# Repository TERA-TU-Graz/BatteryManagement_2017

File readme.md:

# Battery Management System (BMS) with use of STM32 CubeMX

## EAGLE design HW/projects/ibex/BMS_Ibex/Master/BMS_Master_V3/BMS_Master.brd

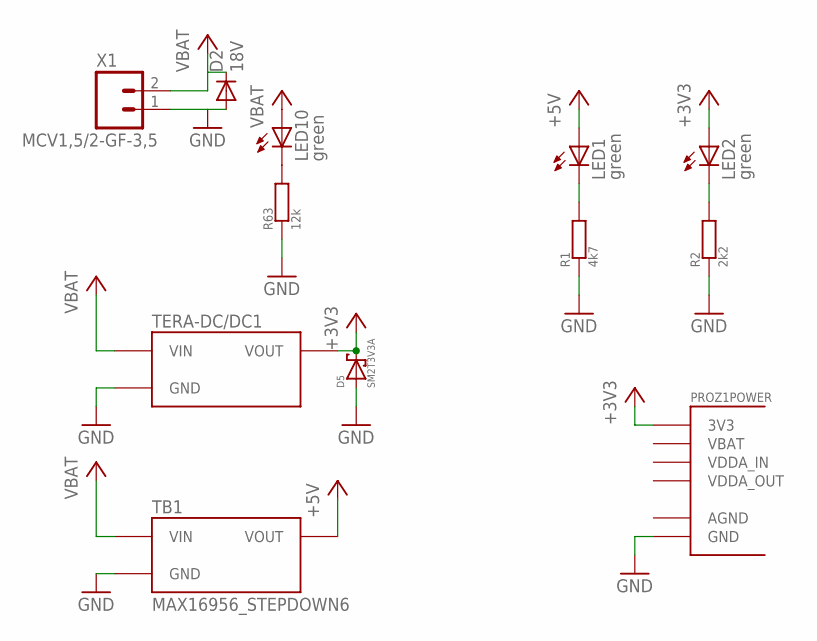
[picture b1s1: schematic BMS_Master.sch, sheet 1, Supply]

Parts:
D2: 18V; DO214AA
D5: SM2T3V3A
LED1, LED2, LED10: green; CHIP-LED0805
PROZ1: STM32F4_PROZESSORBOARDRPZ; STM32F4_PROZESSORBOARD
R1: 4k7; R0805
R2: 2k2; R0805
R63: 12k; R0805
TB1: MAX16956_STEPDOWN6
TERA-DC/DC1: MAX5035_STEPDOWN3
X1: MCV1,5/2-GF-3,5

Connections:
+3V3: D5.P$2, LED2.A, PROZ1.45 (3V3), PROZ1.46 (3V3), TERA-DC/DC1.VOUT; also elsewhere on the board
+5V: LED1.A, TB1.VOUT; also elsewhere on the board
GND: D2.A, D5.P$1, D5.P$11, PROZ1.47 (GND), PROZ1.48 (GND), R1.1, R2.1, R63.1, TB1.GND, TB1.GND2 (GND), TERA-DC/DC1.GND@1 (GND), TERA-DC/DC1.GND@2 (GND), X1.1; also elsewhere on the board
unnamed: LED1.C, R1.2
unnamed: LED2.C, R2.2
unnamed: LED10.C, R63.2
VBAT: D2.C, LED10.A, TB1.VIN, TERA-DC/DC1.VIN, X1.2; also elsewhere on the board

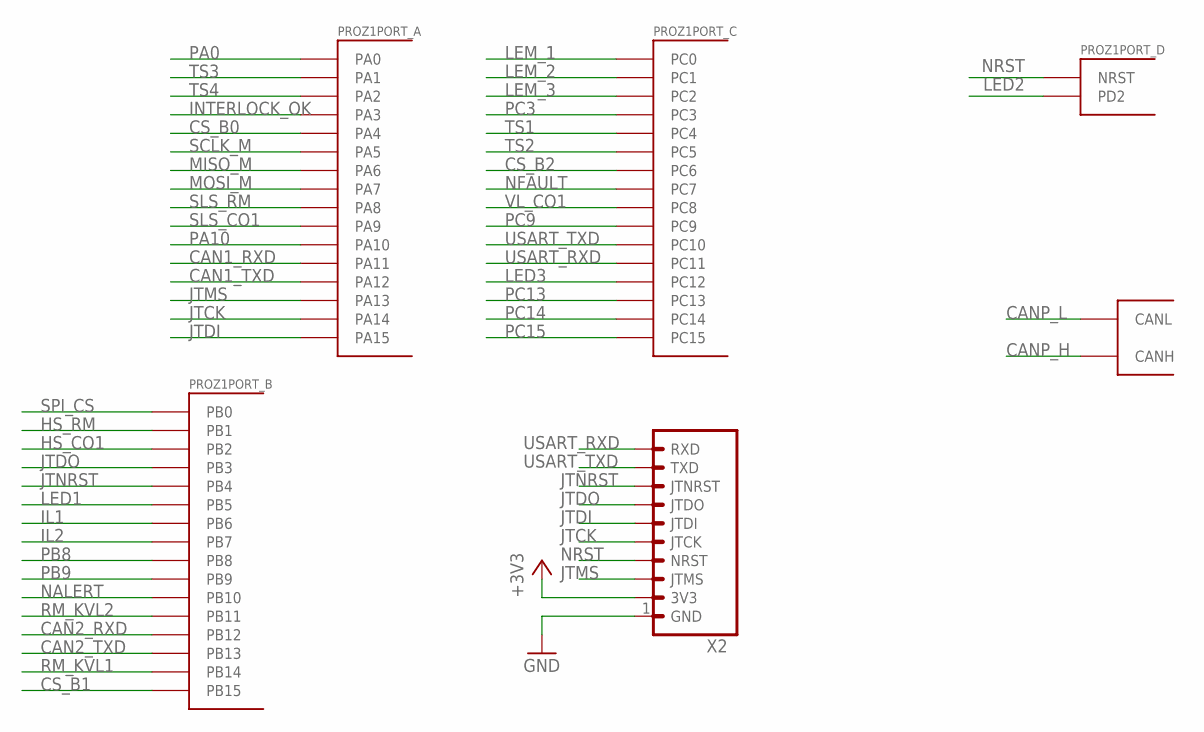
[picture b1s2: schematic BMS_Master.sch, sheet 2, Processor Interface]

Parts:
PROZ1: STM32F4_PROZESSORBOARDRPZ; STM32F4_PROZESSORBOARD
X2: TERA-PROG-DEBUG-10GERADE; 90130-1110

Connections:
+3V3: X2.2 (3V3); also elsewhere on the board
CAN1_RXD: PROZ1.26 (PA11); also elsewhere on the board
CAN1_TXD: PROZ1.24 (PA12); also elsewhere on the board
CAN2_RXD: PROZ1.50 (PB12); also elsewhere on the board
CAN2_TXD: PROZ1.49 (PB13); also elsewhere on the board
CANP_H: PROZ1.31 (CANH); also elsewhere on the board
CANP_L: PROZ1.32 (CANL); also elsewhere on the board
CS_B0: PROZ1.43 (PA4); also elsewhere on the board
CS_B1: PROZ1.51 (PB15); also elsewhere on the board
CS_B2: PROZ1.52 (PC6); also elsewhere on the board
GND: X2.1 (GND); also elsewhere on the board
HS_CO1: PROZ1.36 (PB2); also elsewhere on the board
HS_RM: PROZ1.37 (PB1); also elsewhere on the board
IL1: PROZ1.14 (PB6); also elsewhere on the board
IL2: PROZ1.12 (PB7); also elsewhere on the board
INTERLOCK_OK: PROZ1.44 (PA3); also elsewhere on the board
JTCK: PROZ1.18 (PA14), X2.5 (JTCK)
JTDI: PROZ1.16 (PA15), X2.6 (JTDI)
JTDO: PROZ1.20 (PB3), X2.7 (JTDO)
JTMS: PROZ1.59 (PA13), X2.3 (JTMS)
JTNRST: PROZ1.22 (PB4), X2.8 (JTNRST)
LED1: PROZ1.25 (PB5)
LED2: PROZ1.27 (PD2)
LED3: PROZ1.29 (PC12)
LEM_1: PROZ1.15 (PC0); also elsewhere on the board
LEM_2: PROZ1.13 (PC1); also elsewhere on the board
LEM_3: PROZ1.11 (PC2); also elsewhere on the board
MISO_M: PROZ1.42 (PA6); also elsewhere on the board
MOSI_M: PROZ1.41 (PA7); also elsewhere on the board
NALERT: PROZ1.35 (PB10); also elsewhere on the board
NFAULT: PROZ1.53 (PC7); also elsewhere on the board
NRST: PROZ1.17 (NRST), X2.4 (NRST)
PA0: PROZ1.7 (PA0)
PA10: PROZ1.58 (PA10)
PB8: PROZ1.10 (PB8)
PB9: PROZ1.8 (PB9)
PC3: PROZ1.9 (PC3)
PC9: PROZ1.55 (PC9)
PC13: PROZ1.23 (PC13)
PC14: PROZ1.21 (PC14)
PC15: PROZ1.19 (PC15)
RM_KVL1: PROZ1.33 (PB14); also elsewhere on the board
RM_KVL2: PROZ1.34 (PB11); also elsewhere on the board
SCLK_M: PROZ1.60 (PA5); also elsewhere on the board
SLS_CO1: PROZ1.57 (PA9); also elsewhere on the board
SLS_RM: PROZ1.56 (PA8); also elsewhere on the board
SPI_CS: PROZ1.38 (PB0); also elsewhere on the board
TS1: PROZ1.40 (PC4); also elsewhere on the board
TS2: PROZ1.39 (PC5); also elsewhere on the board
TS3: PROZ1.5 (PA1); also elsewhere on the board
TS4: PROZ1.3 (PA2); also elsewhere on the board
USART_RXD: PROZ1.30 (PC11), X2.10 (RXD)
USART_TXD: PROZ1.28 (PC10), X2.9 (TXD)
VL_CO1: PROZ1.54 (PC8); also elsewhere on the board

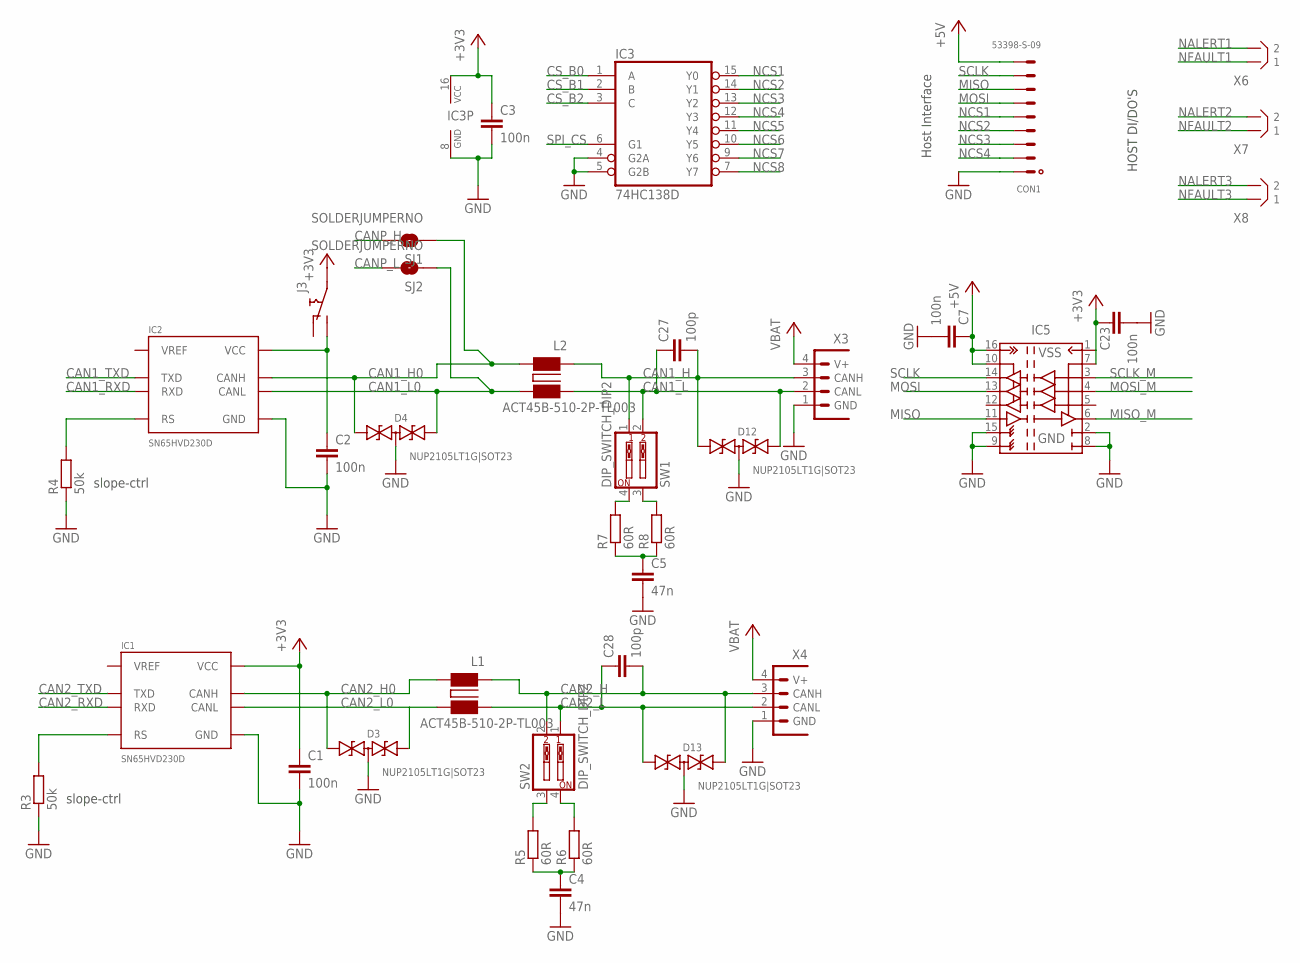
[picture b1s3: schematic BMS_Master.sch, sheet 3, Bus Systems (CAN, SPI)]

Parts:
C1, C2, C3: 100n; C0805
C4, C5: 47n; C0603
C7, C23: 100n; C0603
C27, C28: 100p; C0603
CON1: 53398-S-09; 53398-09-S
D3, D4, D12, D13: NUP2105LT1G|SOT23; SOT23
IC1, IC2: SN65HVD230D; SO08
IC3: 74HC138D; SO16
IC5: ISO7241; R-PDSO-G16
J3: JUMPER_SWITCHS; J_OR_S
L1, L2: ACT45B-510-2P-TL003; ACT45B
R3, R4: 50k; R0805
R5, R6, R7, R8: 60R; R0603
SJ1, SJ2: SOLDERJUMPERNO; SJ_2S-NO
SW1, SW2: DIP_SWITCH_DIP2; DIPSWITCH-02
X3, X4: CIOC_4-1-FV-A_CAN-BELEGUNG; CIOC_4-1-FV
X6, X7, X8: B2B-XH

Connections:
+3V3: C1.1, C3.1, C23.2, IC1.3 (VCC), IC3.16 (VCC), IC5.1 (VCC1), IC5.7 (EN1), J3.P$1; also elsewhere on the board
+5V: C7.2, CON1.9, IC5.10 (EN2), IC5.16 (VCC2); also elsewhere on the board
CAN1_H: C27.2, D12.1, L2.P$3 (3), SW1.1, X3.3 (CANH)
CAN1_H0: D4.1, IC2.7 (CANH), L2.P$4 (4), SJ1.1
CAN1_L: C27.1, D12.2, L2.P$1 (1), SW1.2, X3.2 (CANL)
CAN1_L0: D4.2, IC2.6 (CANL), L2.P$2 (2), SJ2.1
CAN1_RXD: IC2.4 (RXD); also elsewhere on the board
CAN1_TXD: IC2.1 (TXD); also elsewhere on the board
CAN2_H: C28.2, D13.2, L1.P$3 (3), SW2.2, X4.3 (CANH)
CAN2_H0: D3.1, IC1.7 (CANH), L1.P$4 (4)
CAN2_L: C28.1, D13.1, L1.P$1 (1), SW2.1, X4.2 (CANL)
CAN2_L0: D3.2, IC1.6 (CANL), L1.P$2 (2)
CAN2_RXD: IC1.4 (RXD); also elsewhere on the board
CAN2_TXD: IC1.1 (TXD); also elsewhere on the board
CANP_H: SJ1.2; also elsewhere on the board
CANP_L: SJ2.2; also elsewhere on the board
CS_B0: IC3.1 (A); also elsewhere on the board
CS_B1: IC3.2 (B); also elsewhere on the board
CS_B2: IC3.3 (C); also elsewhere on the board
GND: C1.2, C2.2, C3.2, C4.2, C5.2, C7.1, C23.1, CON1.1, D3.3, D4.3, D12.3, D13.3, IC1.2 (GND), IC2.2 (GND), IC3.4 (G2A), IC3.5 (G2B), IC3.8 (GND), IC5.2 (GND11), IC5.8 (GND12), IC5.9 (GND22), IC5.15 (GND21), R3.1, R4.1, X3.1 (GND), X4.1 (GND); also elsewhere on the board
MISO: CON1.7, IC5.11 (IN_D); also elsewhere on the board
MISO_M: IC5.6 (OUT_D); also elsewhere on the board
MOSI: CON1.6, IC5.13 (OUT_B); also elsewhere on the board
MOSI_M: IC5.4 (IN_B); also elsewhere on the board
unnamed: C5.1, R7.1, R8.1
unnamed: C2.1, IC2.3 (VCC), J3.P$2
unnamed: IC2.8 (RS), R4.2
unnamed: C4.1, R5.1, R6.1
unnamed: R7.2, SW1.4
unnamed: IC1.8 (RS), R3.2
unnamed: R5.2, SW2.3
unnamed: R6.2, SW2.4
unnamed: R8.2, SW1.3
NALERT1: X6.P$2 (2); also elsewhere on the board
NALERT2: X7.P$2 (2); also elsewhere on the board
NALERT3: X8.P$2 (2); also elsewhere on the board
NCS1: CON1.5, IC3.15 (Y0)
NCS2: CON1.4, IC3.14 (Y1)
NCS3: CON1.3, IC3.13 (Y2)
NCS4: CON1.2, IC3.12 (Y3)
NCS5: IC3.11 (Y4)
NCS6: IC3.10 (Y5); also elsewhere on the board
NCS7: IC3.9 (Y6); also elsewhere on the board
NCS8: IC3.7 (Y7); also elsewhere on the board
NFAULT1: X6.P$1 (1); also elsewhere on the board
NFAULT2: X7.P$1 (1); also elsewhere on the board
NFAULT3: X8.P$1 (1); also elsewhere on the board
SCLK: CON1.8, IC5.14 (OUT_A); also elsewhere on the board
SCLK_M: IC5.3 (IN_A); also elsewhere on the board
SPI_CS: IC3.6 (G1); also elsewhere on the board
VBAT: X3.4 (V+), X4.4 (V+); also elsewhere on the board

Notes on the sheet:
slope-ctrl
Host Interface
HOST DI/DO'S

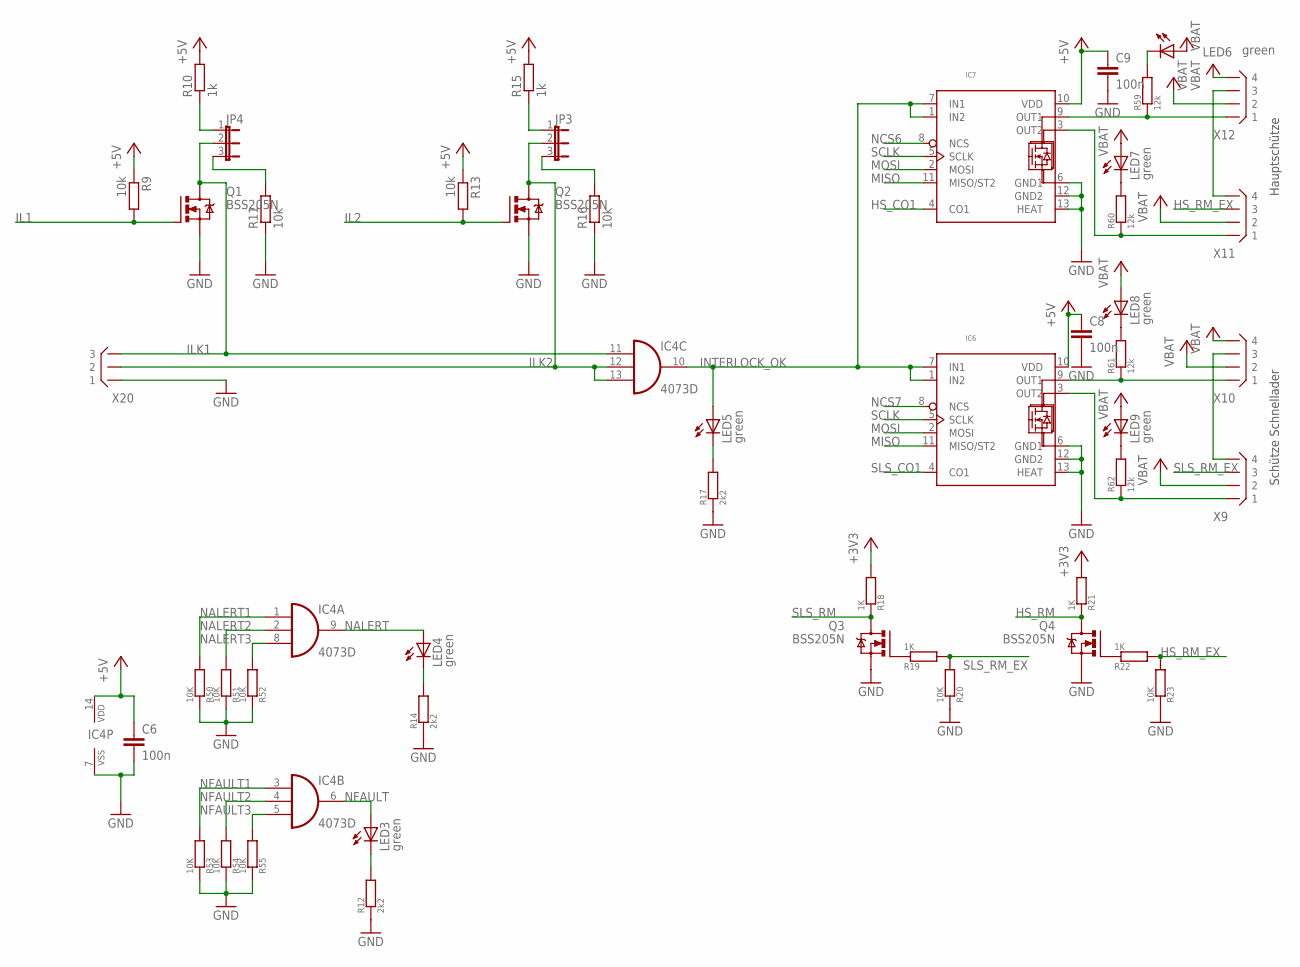
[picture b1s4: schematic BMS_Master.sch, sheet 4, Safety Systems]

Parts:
C6, C8, C9: 100n; C0603
IC4: 4073D; SO14
IC6, IC7: TLE8102SGN; INF-PG-DSO-12-11_N_1PRIMARY
JP3, JP4: JUMPER_OR; JP2_OCT
LED3, LED4, LED5: green; CHIPLED_0805
LED6, LED7, LED8, LED9: green; CHIP-LED0805
Q1, Q2, Q3, Q4: BSS205N; SOT23
R9, R11, R13, R16: 10k; R0603
R10, R15: 1k; R0603
R12, R14, R17: 2k2; R0805
R18, R21: 1K; R0603
R19, R22: 1K; R0805
R20, R23: 10K; R0805
R50, R51, R52, R53, R54, R55: 10K; R0603
R59, R60, R61, R62: 12k; R0805
X9, X10, X11, X12: B4B-XH
X20: B3B-XH

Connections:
+3V3: R18.2, R21.2; also elsewhere on the board
+5V: C6.1, C8.1, C9.1, IC4.14 (VDD), IC6.10 (VDD), IC7.10 (VDD), R9.1, R10.2, R13.1, R15.2; also elsewhere on the board
GND: C6.2, C8.2, C9.2, IC4.7 (VSS), IC6.6 (GND1), IC6.12 (GND2), IC6.13 (HEAT), IC7.6 (GND1), IC7.12 (GND2), IC7.13 (HEAT), Q1.2 (S), Q2.2 (S), Q3.2 (S), Q4.2 (S), R11.1, R12.1, R14.1, R16.1, R17.1, R20.1, R23.1, R50.1, R51.1, R52.1, R53.1, R54.1, R55.1, X20.P$1 (1); also elsewhere on the board
HS_CO1: IC7.4 (CO1); also elsewhere on the board
HS_RM: Q4.3 (D), R21.1; also elsewhere on the board
HS_RM_EX: R22.2, R23.2, X11.P$3 (3)
IL1: Q1.1 (G), R9.2; also elsewhere on the board
IL2: Q2.1 (G), R13.2; also elsewhere on the board
ILK1: IC4.11 (I0), JP4.2, Q1.3 (D), X20.P$3 (3)
ILK2: IC4.12 (I1), IC4.13 (I2), JP3.2, Q2.3 (D), X20.P$2 (2)
INTERLOCK_OK: IC4.10 (O), IC6.1 (IN2), IC6.7 (IN1), IC7.1 (IN2), IC7.7 (IN1), LED5.A; also elsewhere on the board
MISO: IC6.11 (MISO/ST2), IC7.11 (MISO/ST2); also elsewhere on the board
MOSI: IC6.2 (MOSI), IC7.2 (MOSI); also elsewhere on the board
unnamed: X9.P$4 (4), X10.P$3 (3)
unnamed: IC7.3 (OUT2), R60.1, X11.P$1 (1)
unnamed: IC6.9 (OUT1), R61.1, X10.P$1 (1)
unnamed: X11.P$4 (4), X12.P$3 (3)
unnamed: IC6.3 (OUT2), R62.1, X9.P$1 (1)
unnamed: IC7.9 (OUT1), R59.1, X12.P$1 (1)
unnamed: JP4.1, R10.1
unnamed: JP3.1, R15.1
unnamed: JP3.3, R16.2
unnamed: JP4.3, R11.2
unnamed: LED5.C, R17.2
unnamed: LED4.C, R14.2
unnamed: LED3.C, R12.2
unnamed: Q3.1 (G), R19.1
unnamed: Q4.1 (G), R22.1
unnamed: LED6.C, R59.2
unnamed: LED7.C, R60.2
unnamed: LED8.C, R61.2
unnamed: LED9.C, R62.2
NALERT: IC4.9 (O), LED4.A; also elsewhere on the board
NALERT1: IC4.1 (I0), R50.2; also elsewhere on the board
NALERT2: IC4.2 (I1), R51.2; also elsewhere on the board
NALERT3: IC4.8 (I2), R52.2; also elsewhere on the board
NCS6: IC7.8 (NCS); also elsewhere on the board
NCS7: IC6.8 (NCS); also elsewhere on the board
NFAULT: IC4.6 (O), LED3.A; also elsewhere on the board
NFAULT1: IC4.3 (I0), R53.2; also elsewhere on the board
NFAULT2: IC4.4 (I1), R54.2; also elsewhere on the board
NFAULT3: IC4.5 (I2), R55.2; also elsewhere on the board
SCLK: IC6.5 (SCLK), IC7.5 (SCLK); also elsewhere on the board
SLS_CO1: IC6.4 (CO1); also elsewhere on the board
SLS_RM: Q3.3 (D), R18.1; also elsewhere on the board
SLS_RM_EX: R19.2, R20.2, X9.P$3 (3)
VBAT: LED6.A, LED7.A, LED8.A, LED9.A, X9.P$2 (2), X10.P$2 (2), X10.P$4 (4), X11.P$2 (2), X12.P$2 (2), X12.P$4 (4); also elsewhere on the board

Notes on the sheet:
Hauptschütze
Schütze Schnellader

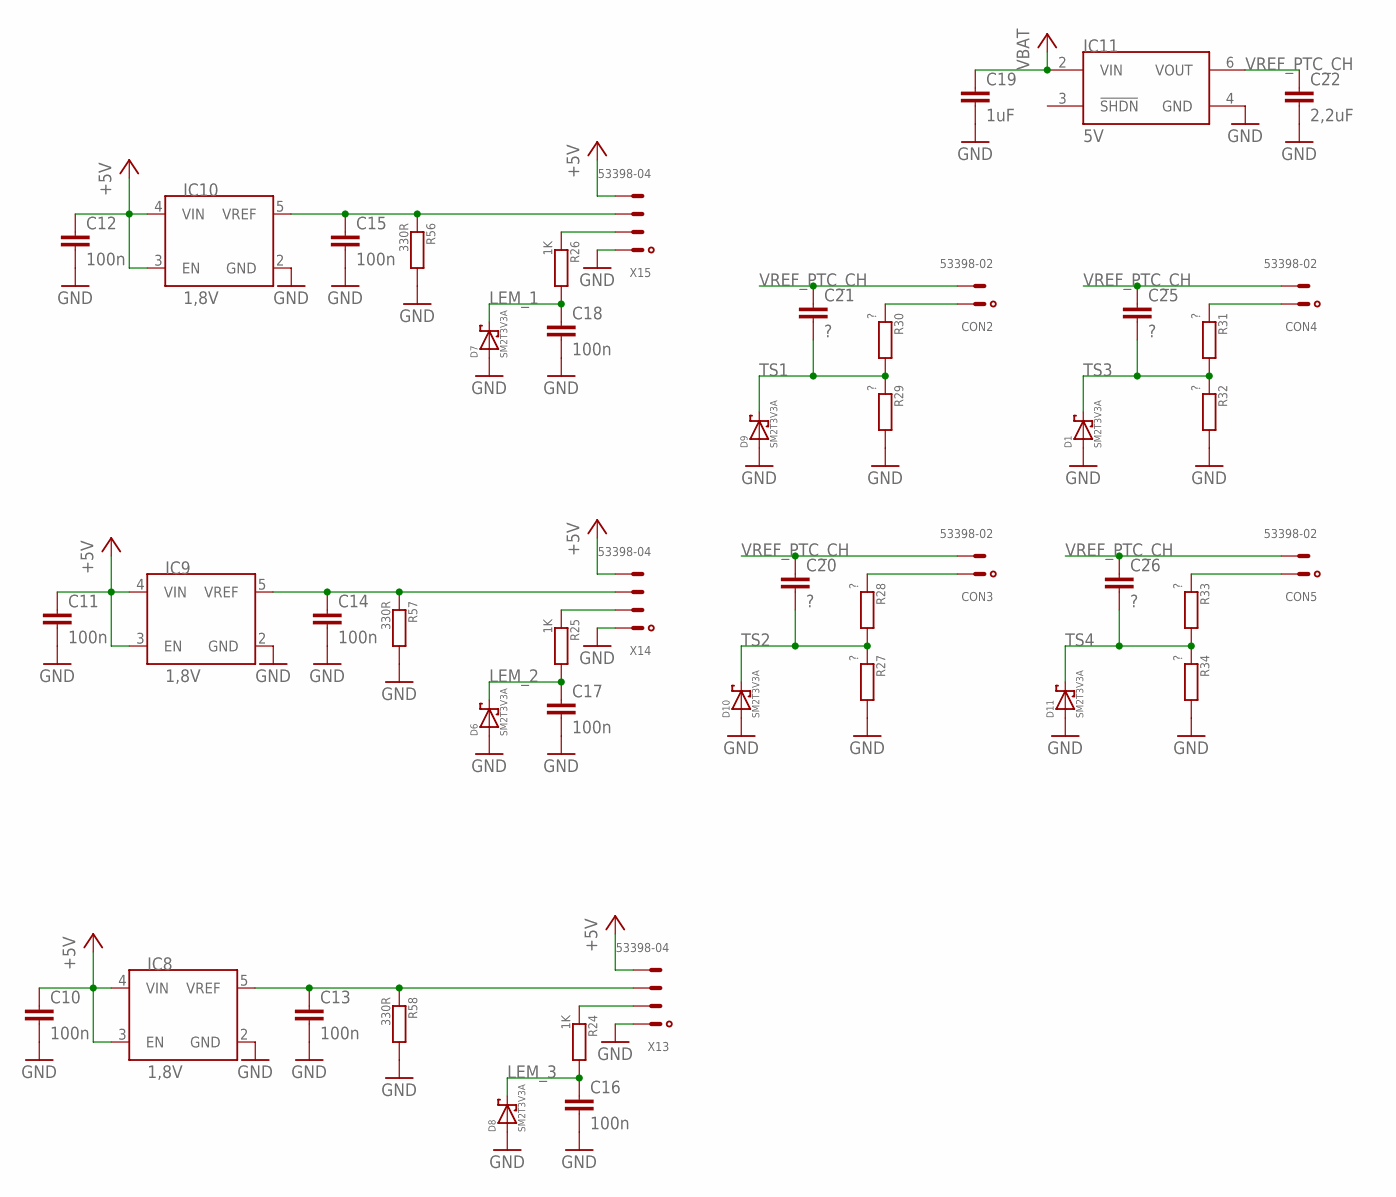
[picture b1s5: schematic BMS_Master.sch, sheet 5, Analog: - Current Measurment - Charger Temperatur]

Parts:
C10, C11, C12, C13, C14, C15, C16, C17, C18: 100n; C0805
C19: 1uF; C0805
C20, C21, C25, C26: ?; C0603
C22: 2,2uF; C0805
CON2, CON3, CON4, CON5: 53398-02
D1, D6, D7, D8, D9, D10, D11: SM2T3V3A
IC8, IC9, IC10: 1,8V; SOT23-5L
IC11: 5V; SO08
R24, R25, R26: 1K; R0805
R27, R28, R29, R30, R31, R32, R33, R34: ?; R0603
R56, R57, R58: 330R; R0805
X13, X14, X15: 53398-04

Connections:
+5V: C10.1, C11.1, C12.1, IC8.3 (EN), IC8.4 (VIN), IC9.3 (EN), IC9.4 (VIN), IC10.3 (EN), IC10.4 (VIN), X13.4, X14.4, X15.4; also elsewhere on the board
GND: C10.2, C11.2, C12.2, C13.2, C14.2, C15.2, C16.2, C17.2, C18.2, C19.2, C22.2, D1.P$1, D1.P$11, D6.P$1, D6.P$11, D7.P$1, D7.P$11, D8.P$1, D8.P$11, D9.P$1, D9.P$11, D10.P$1, D10.P$11, D11.P$1, D11.P$11, IC8.2 (GND), IC9.2 (GND), IC10.2 (GND), IC11.4 (GND), R27.2, R29.2, R32.2, R34.2, R56.2, R57.2, R58.2, X13.1, X14.1, X15.1; also elsewhere on the board
LEM_1: C18.1, D7.P$2, R26.2; also elsewhere on the board
LEM_2: C17.1, D6.P$2, R25.2; also elsewhere on the board
LEM_3: C16.1, D8.P$2, R24.2; also elsewhere on the board
unnamed: C13.1, IC8.5 (VREF), R58.1, X13.3
unnamed: R26.1, X15.2
unnamed: C14.1, IC9.5 (VREF), R57.1, X14.3
unnamed: CON4.1, R31.1
unnamed: CON5.1, R33.1
unnamed: CON2.1, R30.1
unnamed: R25.1, X14.2
unnamed: C15.1, IC10.5 (VREF), R56.1, X15.3
unnamed: R24.1, X13.2
unnamed: CON3.1, R28.1
TS1: C21.2, D9.P$2, R29.1, R30.2; also elsewhere on the board
TS2: C20.2, D10.P$2, R27.1, R28.2; also elsewhere on the board
TS3: C25.2, D1.P$2, R31.2, R32.1; also elsewhere on the board
TS4: C26.2, D11.P$2, R33.2, R34.1; also elsewhere on the board
VBAT: C19.1, IC11.2 (VIN); also elsewhere on the board
VREF_PTC_CH: C20.1, C21.1, C22.1, C25.1, C26.1, CON2.2, CON3.2, CON4.2, CON5.2, IC11.6 (VOUT)

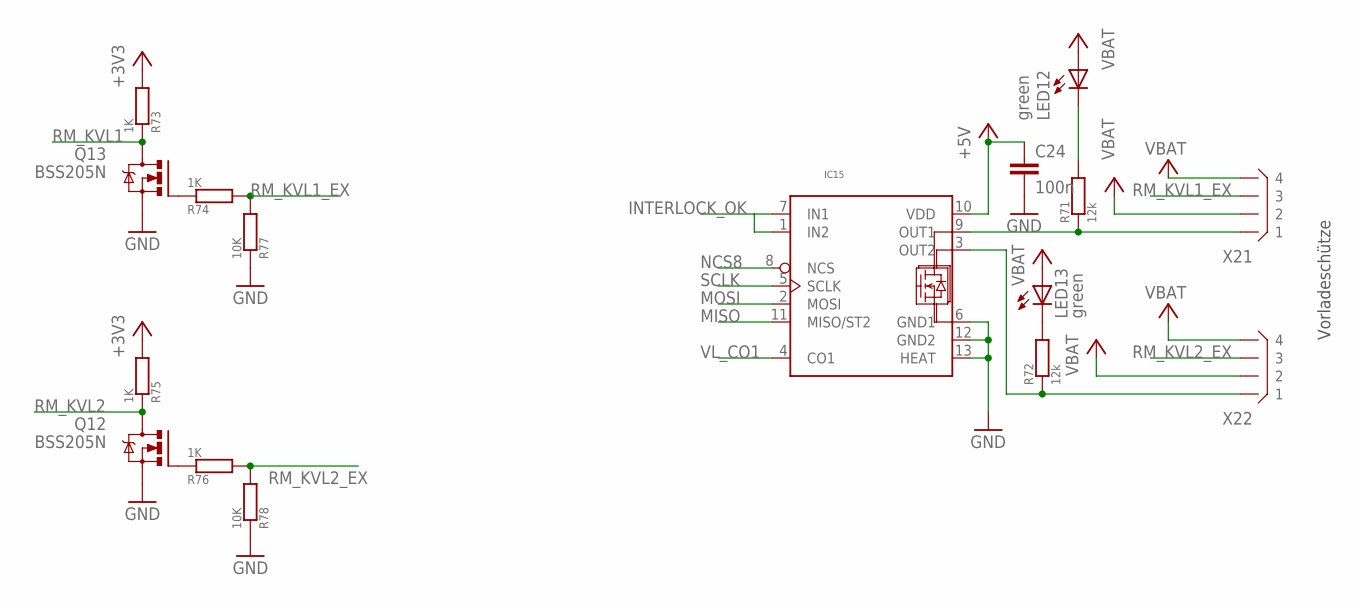
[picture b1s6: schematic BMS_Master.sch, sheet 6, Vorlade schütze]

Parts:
C24: 100n; C0603
IC15: TLE8102SGN; INF-PG-DSO-12-11_N_1PRIMARY
LED12, LED13: green; CHIP-LED0805
Q12, Q13: BSS205N; SOT23
R71, R72: 12k; R0805
R73, R74, R75, R76: 1K; R0805
R77, R78: 10K; R0805
X21, X22: B4B-XH

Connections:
+3V3: R73.2, R75.2; also elsewhere on the board
+5V: C24.1, IC15.10 (VDD); also elsewhere on the board
GND: C24.2, IC15.6 (GND1), IC15.12 (GND2), IC15.13 (HEAT), Q12.2 (S), Q13.2 (S), R77.1, R78.1; also elsewhere on the board
INTERLOCK_OK: IC15.1 (IN2), IC15.7 (IN1); also elsewhere on the board
MISO: IC15.11 (MISO/ST2); also elsewhere on the board
MOSI: IC15.2 (MOSI); also elsewhere on the board
unnamed: IC15.3 (OUT2), R72.1, X22.P$1 (1)
unnamed: IC15.9 (OUT1), R71.1, X21.P$1 (1)
unnamed: LED12.C, R71.2
unnamed: LED13.C, R72.2
unnamed: Q12.1 (G), R76.1
unnamed: Q13.1 (G), R74.1
NCS8: IC15.8 (NCS); also elsewhere on the board
RM_KVL1: Q13.3 (D), R73.1; also elsewhere on the board
RM_KVL1_EX: R74.2, R77.2, X21.P$3 (3)
RM_KVL2: Q12.3 (D), R75.1; also elsewhere on the board
RM_KVL2_EX: R76.2, R78.2, X22.P$3 (3)
SCLK: IC15.5 (SCLK); also elsewhere on the board
VBAT: LED12.A, LED13.A, X21.P$2 (2), X21.P$4 (4), X22.P$2 (2), X22.P$4 (4); also elsewhere on the board
VL_CO1: IC15.4 (CO1); also elsewhere on the board

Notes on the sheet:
Vorladeschütze

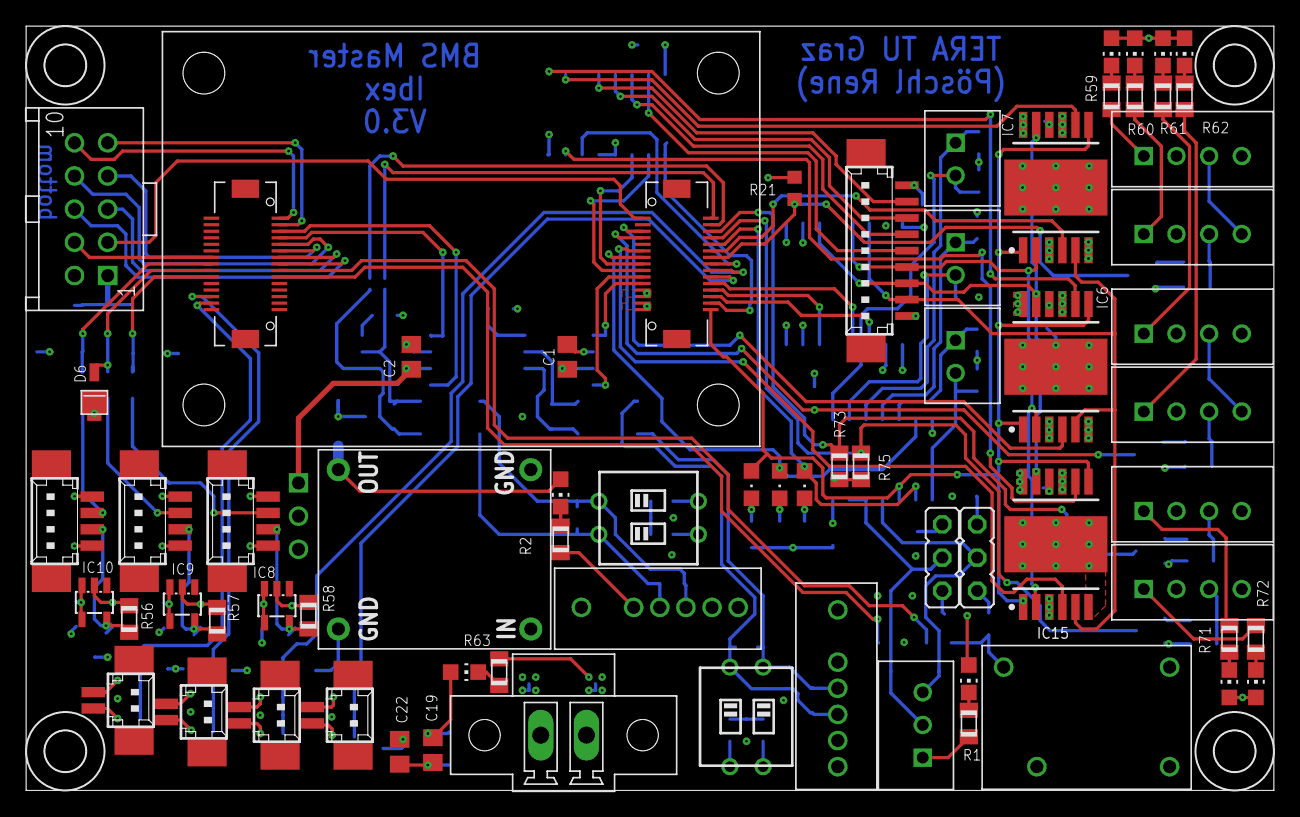
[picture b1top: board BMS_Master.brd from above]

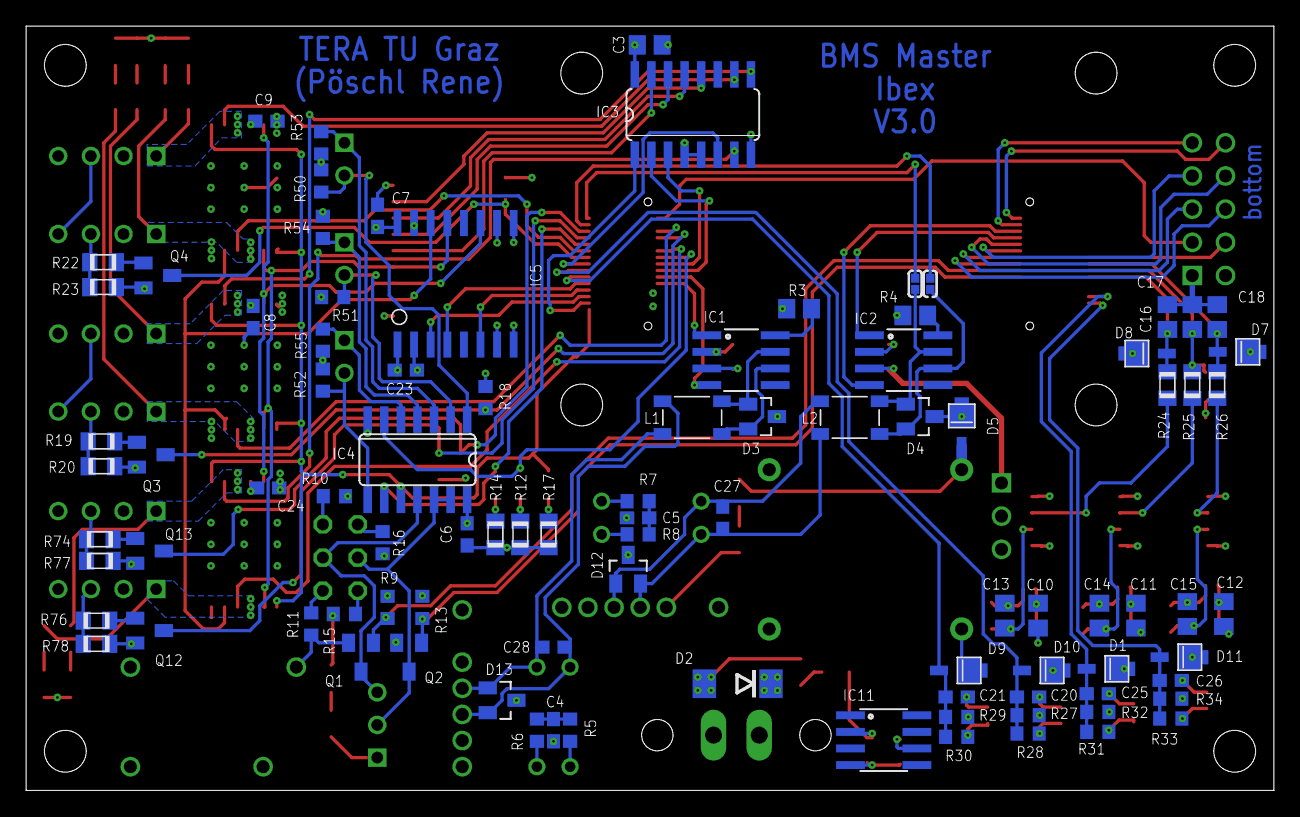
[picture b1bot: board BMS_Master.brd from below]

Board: 4 copper layers, 95.5 x 58.5 mm, 165 parts (93 on the bottom side), 122 nets.

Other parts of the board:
H1, H2, H3, H4: MOUNT-HOLE3.2; 3,2

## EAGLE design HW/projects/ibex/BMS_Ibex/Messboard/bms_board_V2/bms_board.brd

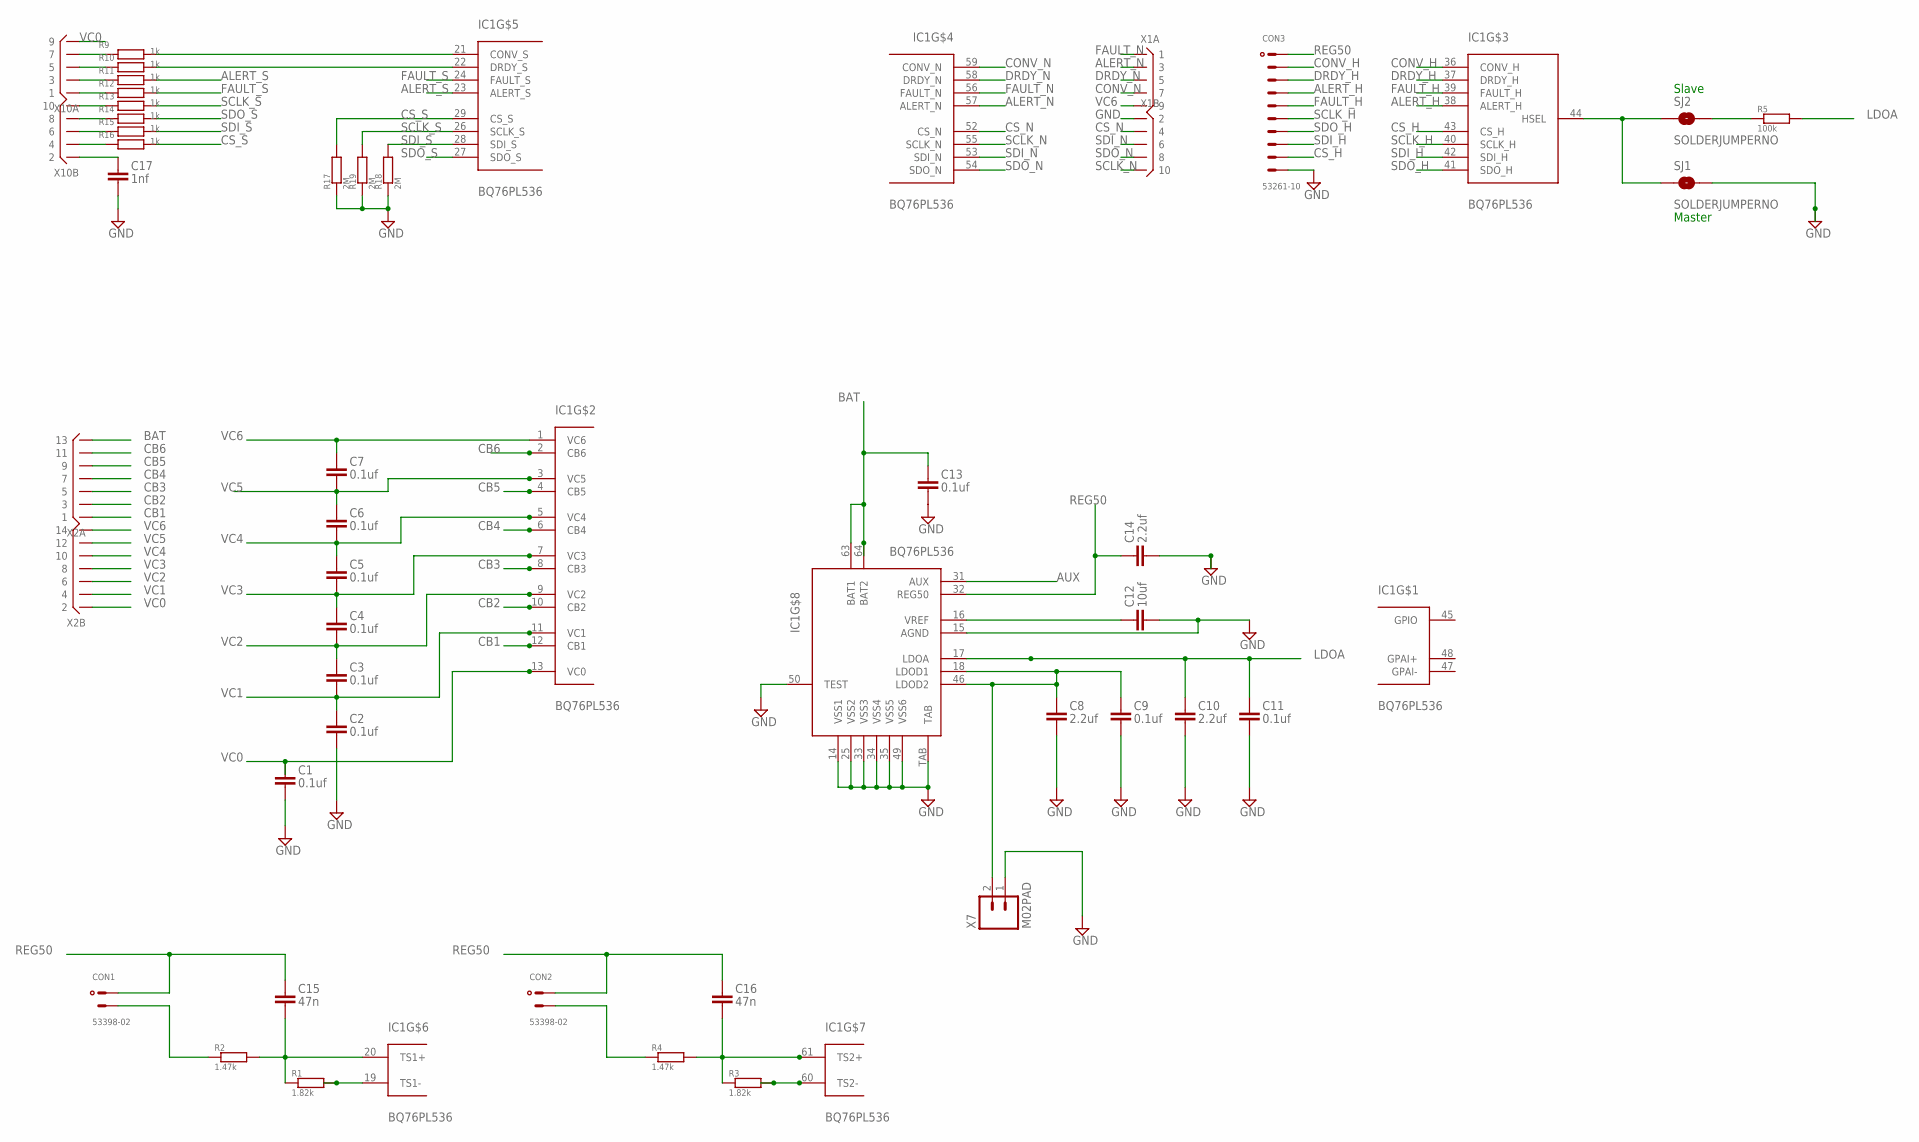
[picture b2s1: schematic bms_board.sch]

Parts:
C1, C2, C3, C4, C5, C6, C7, C9, C11, C13: 0.1uf; C0805
C8, C10, C14: 2.2uf; C0805
C12: 10uf; C0805
C15, C16: 47n; C0805
C17: 1nf; C0805
CON1, CON2: 53398-02
CON3: 53261-10
IC1: BQ76PL536; LQFP-64
R1, R3: 1.82k; R0805
R2, R4: 1.47k; R0805
R5: 100k; R0805
R9, R10, R11, R12, R13, R14, R15, R16: 1k; R0805
R17, R18, R19: 2M; R0805
SJ1, SJ2: SOLDERJUMPERNO; SJ_2S-NO
X1, X10: X05X2ICR; X10ICR
X2: X07X2IR; X14R-IDC
X7: M02PAD; 1X02

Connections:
ALERT_H: CON3.4, IC1.38 (ALERT_H)
ALERT_N: IC1.57 (ALERT_N), X1.3
ALERT_S: IC1.23 (ALERT_S), R11.2
AUX: IC1.31 (AUX)
BAT: C13.2, IC1.63 (BAT1), IC1.64 (BAT2), X2.13
CB1: IC1.12 (CB1), X2.1
CB2: IC1.10 (CB2), X2.3
CB3: IC1.8 (CB3), X2.5
CB4: IC1.6 (CB4), X2.7
CB5: IC1.4 (CB5), X2.9
CB6: IC1.2 (CB6), X2.11
CONV_H: CON3.2, IC1.36 (CONV_H)
CONV_N: IC1.59 (CONV_N), X1.7
CONV_S: IC1.21 (CONV_S), R9.2
CS_H: CON3.9, IC1.43 (CS_H)
CS_N: IC1.52 (CS_N), X1.4
CS_S: IC1.29 (CS_S), R16.2, R17.2
DRDY_H: CON3.3, IC1.37 (DRDY_H)
DRDY_N: IC1.58 (DRDY_N), X1.5
DRDY_S: IC1.22 (DRDY_S), R10.2
FAULT_H: CON3.5, IC1.39 (FAULT_H)
FAULT_N: IC1.56 (FAULT_N), X1.1
FAULT_S: IC1.24 (FAULT_S), R12.2
GND: C1.1, C2.1, C8.1, C9.1, C10.1, C11.1, C12.1, C13.1, C14.1, C17.1, CON3.10, IC1.14 (VSS1), IC1.15 (AGND), IC1.25 (VSS2), IC1.33 (VSS3), IC1.34 (VSS4), IC1.35 (VSS5), IC1.49 (VSS6), IC1.50 (TEST), IC1.TAB, R17.1, R18.1, R19.1, SJ1.2, X1.2, X7.1
LDOA: C10.2, C11.2, IC1.17 (LDOA), R5.2
unnamed: IC1.44 (HSEL), SJ1.1, SJ2.1
unnamed: C8.2, C9.2, IC1.18 (LDOD1), IC1.46 (LDOD2), X7.2
unnamed: C12.2, IC1.16 (VREF)
unnamed: IC1.19 (TS1-), R1.2
unnamed: CON1.2, R2.1
unnamed: C15.1, IC1.20 (TS1+), R1.1, R2.2
unnamed: IC1.60 (TS2-), R3.2
unnamed: C16.1, IC1.61 (TS2+), R3.1, R4.2
unnamed: CON2.2, R4.1
unnamed: R5.1, SJ2.2
unnamed: R16.1, X10.4
unnamed: R15.1, X10.6
unnamed: R14.1, X10.8
unnamed: R13.1, X10.10
unnamed: R12.1, X10.1
unnamed: R11.1, X10.3
unnamed: R10.1, X10.5
unnamed: R9.1, X10.7
unnamed: C17.2, X10.2
REG50: C14.2, C15.2, C16.2, CON1.1, CON2.1, CON3.1, IC1.32 (REG50)
SCLK_H: CON3.6, IC1.40 (SCLK_H)
SCLK_N: IC1.55 (SCLK_N), X1.10
SCLK_S: IC1.26 (SCLK_S), R13.2, R19.2
SDI_H: CON3.8, IC1.42 (SDI_H)
SDI_N: IC1.53 (SDI_N), X1.6
SDI_S: IC1.28 (SDI_S), R15.2, R18.2
SDO_H: CON3.7, IC1.41 (SDO_H)
SDO_N: IC1.54 (SDO_N), X1.8
SDO_S: IC1.27 (SDO_S), R14.2
VC0: C1.2, IC1.13 (VC0), X2.2, X10.9
VC1: C2.2, C3.1, IC1.11 (VC1), X2.4
VC2: C3.2, C4.1, IC1.9 (VC2), X2.6
VC3: C4.2, C5.1, IC1.7 (VC3), X2.8
VC4: C5.2, C6.1, IC1.5 (VC4), X2.10
VC5: C6.2, C7.1, IC1.3 (VC5), X2.12
VC6: C7.2, IC1.1 (VC6), X1.9, X2.14

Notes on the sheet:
Master
Slave

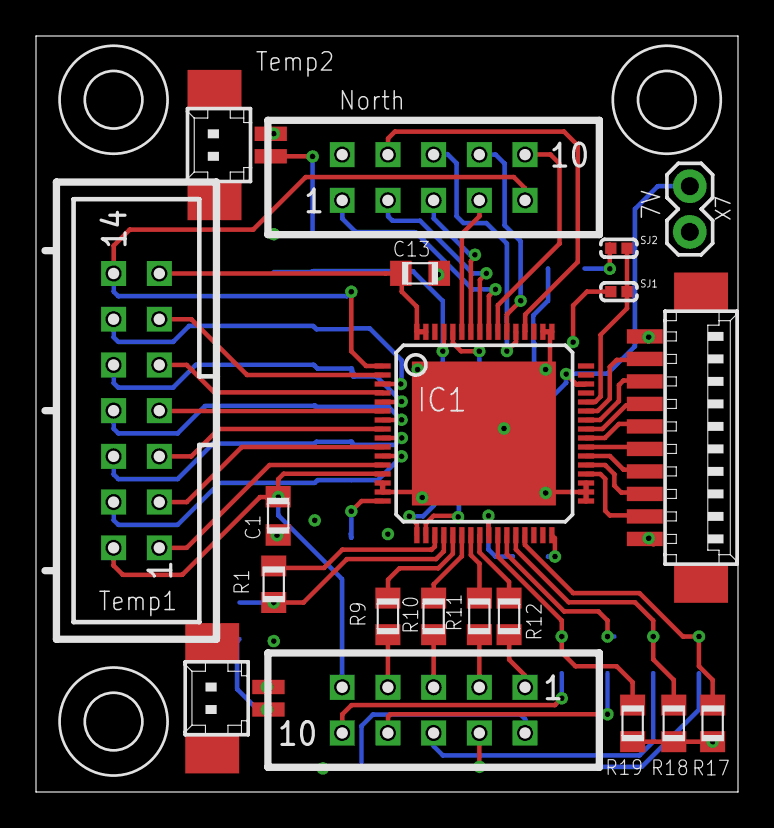
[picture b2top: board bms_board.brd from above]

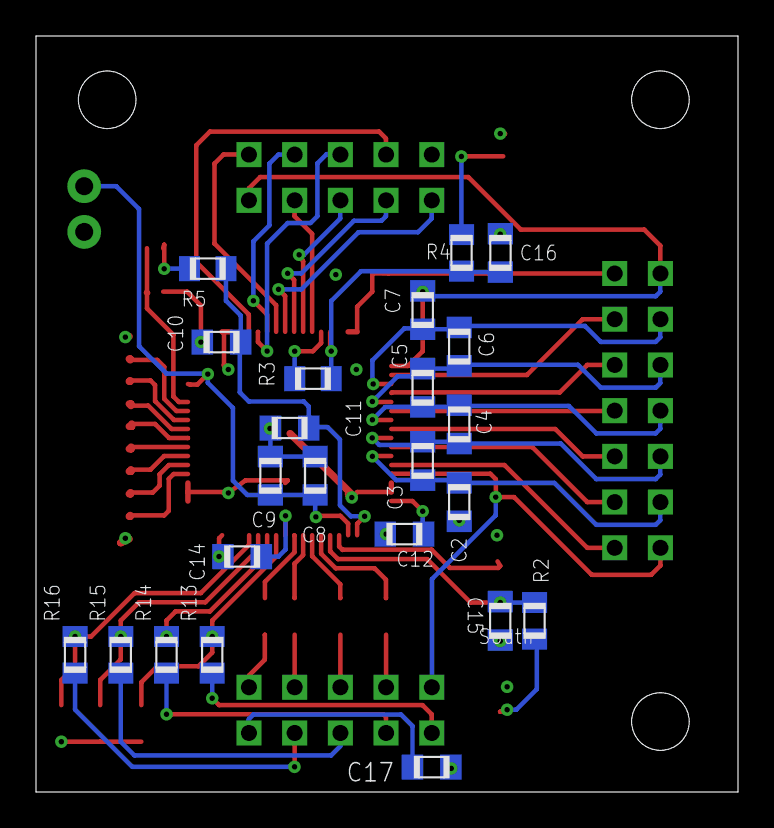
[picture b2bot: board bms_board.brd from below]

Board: 4 copper layers, 39.0 x 42.0 mm, 46 parts (23 on the bottom side), 60 nets.

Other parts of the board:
U$3, U$4, U$6: 3,2

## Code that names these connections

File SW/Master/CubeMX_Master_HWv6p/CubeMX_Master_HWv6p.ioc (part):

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Mcu.Name=STM32F405RGTx
Mcu.Package=LQFP64
Mcu.UserName=STM32F405RGTx
PA1.GPIOParameters=GPIO_Label
PA1.GPIO_Label=LEM1
PA1.Signal=ADCx_IN1
PA10.GPIOParameters=GPIO_Label
PA10.GPIO_Label=CAN1_RS
PA10.Signal=GPIO_Output
PA11.Mode=Master
PA11.Signal=CAN1_RX
PA12.Mode=Master
PA12.Signal=CAN1_TX
PA13.Mode=JTAG_5_pins
PA13.Signal=SYS_JTMS-SWDIO
PA14.Mode=JTAG_5_pins
PA14.Signal=SYS_JTCK-SWCLK
PA15.Mode=JTAG_5_pins
PA15.Signal=SYS_JTDI
PA2.GPIOParameters=GPIO_Label
PA2.GPIO_Label=LEM2
PA2.Signal=ADCx_IN2
PA3.GPIOParameters=GPIO_Label
PA3.GPIO_Label=WHEEL_SPEED
PA3.Signal=S_TIM2_CH4
PA4.GPIOParameters=GPIO_Label,GPIO_ModeDefaultOutputPP
PA4.GPIO_Label=SPI1_CS_B0
PA4.GPIO_ModeDefaultOutputPP=GPIO_MODE_OUTPUT_OD
PA4.Signal=GPIO_Output
PA5.Mode=Full_Duplex_Master
PA5.Signal=SPI1_SCK
PA6.Mode=Full_Duplex_Master
PA6.Signal=SPI1_MISO
PA7.Mode=Full_Duplex_Master
PA7.Signal=SPI1_MOSI
PA8.GPIOParameters=GPIO_Label
PA8.GPIO_Label=SuperCharger_On
PA8.Signal=GPIO_Input
PA9.GPIOParameters=GPIO_Label
PA9.GPIO_Label=SuperCharger_Fault
PA9.Signal=GPIO_Input
PB0.GPIOParameters=GPIO_Speed,GPIO_Label,GPIO_ModeDefaultOutputPP
PB0.GPIO_Label=SPI1_CS
PB0.GPIO_ModeDefaultOutputPP=GPIO_MODE_OUTPUT_OD
PB0.GPIO_Speed=GPIO_SPEED_FREQ_HIGH
PB0.Signal=GPIO_Output
PB1.GPIOParameters=GPIO_Label
PB1.GPIO_Label=Main_on
PB1.Signal=GPIO_Input
PB10.GPIOParameters=GPIO_Label
PB10.GPIO_Label=N_Alert
PB10.Signal=GPIO_Input
PB11.GPIOParameters=GPIO_Label
PB11.GPIO_Label=FAN_Fault
PB11.Signal=GPIO_Input
PB12.Mode=Slave
PB12.Signal=CAN2_RX
PB13.Mode=Slave
PB13.Signal=CAN2_TX
PB14.GPIOParameters=GPIO_Label
PB14.GPIO_Label=CAN2_RS
PB14.Signal=GPIO_Output
PB15.GPIOParameters=GPIO_Label,GPIO_ModeDefaultOutputPP
PB15.GPIO_Label=SPI1_CS_B1
PB15.GPIO_ModeDefaultOutputPP=GPIO_MODE_OUTPUT_OD
PB15.Signal=GPIO_Output
PB2.GPIOParameters=GPIO_Label
PB2.GPIO_Label=Main_fault
PB2.Signal=GPIO_Input
PB3.Mode=JTAG_5_pins
PB3.Signal=SYS_JTDO-SWO
PB4.Mode=JTAG_5_pins
PB4.Signal=SYS_JTRST
PB5.GPIOParameters=GPIO_Label
PB5.GPIO_Label=LED1
PB5.Signal=GPIO_Output
PB6.GPIOParameters=GPIO_Label
PB6.GPIO_Label=Interlock_On1
PB6.Signal=GPIO_Output
PB7.GPIOParameters=GPIO_Label
PB7.GPIO_Label=Interlock_On2
PB7.Signal=GPIO_Output
PC0.GPIOParameters=GPIO_Label
PC0.GPIO_Label=TS1
PC0.Signal=ADCx_IN10
PC1.GPIOParameters=GPIO_Label
PC1.GPIO_Label=TS2
PC1.Signal=ADCx_IN11
PC10.Mode=Asynchronous
PC10.Signal=UART4_TX
PC11.Mode=Asynchronous
PC11.Signal=UART4_RX
PC12.GPIOParameters=GPIO_Label
PC12.GPIO_Label=LED3
PC12.Signal=GPIO_Output
PC13-ANTI_TAMP.GPIOParameters=GPIO_PuPd,GPIO_Label
PC13-ANTI_TAMP.GPIO_Label=BUTTON_ON
PC13-ANTI_TAMP.GPIO_PuPd=GPIO_PULLDOWN
PC13-ANTI_TAMP.Signal=GPIO_Input
PC14-OSC32_IN.GPIOParameters=GPIO_PuPd,GPIO_Label
PC14-OSC32_IN.GPIO_Label=BUTTON_OFF
PC14-OSC32_IN.GPIO_PuPd=GPIO_PULLDOWN
PC14-OSC32_IN.Signal=GPIO_Input
PC2.GPIOParameters=GPIO_Label
PC2.GPIO_Label=TS3
PC2.Signal=ADCx_IN12
PC3.GPIOParameters=GPIO_Label
PC3.GPIO_Label=TS4
PC3.Signal=ADCx_IN13
PC4.GPIOParameters=GPIO_PuPd,GPIO_Label
PC4.GPIO_Label=Interlock_OK
PC4.GPIO_PuPd=GPIO_PULLDOWN
PC4.Signal=GPIO_Input
PC5.GPIOParameters=GPIO_Label
PC5.GPIO_Label=N_TMP_REF_SHDN
PC5.Signal=GPIO_Output
PC6.GPIOParameters=GPIO_Label,GPIO_ModeDefaultOutputPP
PC6.GPIO_Label=SPI1_CS_B2
PC6.GPIO_ModeDefaultOutputPP=GPIO_MODE_OUTPUT_OD
PC6.Signal=GPIO_Output
PC7.GPIOParameters=GPIO_Label
PC7.GPIO_Label=N_Fault
PC7.Signal=GPIO_Input
PC8.GPIOParameters=GPIO_Label
PC8.GPIO_Label=Precharge_fault
PC8.Signal=GPIO_Input
PC9.GPIOParameters=GPIO_Label
PC9.GPIO_Label=FAN_PWM
PC9.Signal=S_TIM3_CH4
PD2.GPIOParameters=GPIO_Label
PD2.GPIO_Label=LED2
PD2.Signal=GPIO_Output
PH0-OSC_IN.Mode=HSE-External-Oscillator
PH0-OSC_IN.Signal=RCC_OSC_IN
PH1-OSC_OUT.Mode=HSE-External-Oscillator
PH1-OSC_OUT.Signal=RCC_OSC_OUT
RCC.HSE_VALUE=8000000
RCC.SYSCLKFreq_VALUE=168000000
RCC.SYSCLKSource=RCC_SYSCLKSOURCE_PLLCLK
board=CubeMX_Master_HWv6p

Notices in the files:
parts and their libraries:
SparkFun: Licensing: CC v3.0 Share-Alike You are welcome to use this library for commercial purposes.
